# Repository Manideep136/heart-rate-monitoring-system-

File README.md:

# heart-rate-monitoring-system

## 📌 Project Overview

The **Heart Rate Monitoring System** is an electronics project designed to measure a person's heart rate in beats per minute (BPM) using a heart rate sensor. The system processes the sensor signal and displays the measured heart rate for easy monitoring.

This project focuses on sensor interfacing, signal processing, microcontroller-based measurement, and electronic circuit design.

## 🎯 Project Objectives

- Measure heart rate in beats per minute (BPM).
- Interface a heart rate sensor with a microcontroller.
- Process sensor signals to estimate heart rate.
- Display the measured heart rate on a suitable output device.
- Design a compact and organized electronic circuit or PCB.
- Develop practical skills in embedded systems and electronics.

## ⚙️ Working Principle

1. **Signal Detection:** The heart rate sensor detects changes associated with blood flow, typically using optical sensing.
2. **Signal Processing:** The sensor signal is processed to identify pulse events.
3. **Heart Rate Calculation:** The system estimates the heart rate in BPM based on the detected pulse intervals.
4. **Output Display:** The calculated heart rate is displayed on an LCD, OLED, serial monitor, or other supported output.
5. **Continuous Monitoring:** The system can repeatedly update the reading while the sensor detects a reliable signal.

### Block Diagram

```text
     Human Finger
          │
          ▼
   Heart Rate Sensor
          │
          ▼
    Microcontroller
          │
          ▼
   Signal Processing
          │
          ▼
   BPM Calculation
          │
          ▼
    Display / Output
```

## 🔧 Main Components

| Component | Function |
|---|---|
| Heart rate sensor | Detects pulse-related signals |
| Microcontroller | Processes sensor data and calculates BPM |
| Display module | Displays the measured heart rate, if used |
| Resistors and capacitors | Support signal conditioning and circuit operation, where required |
| Power supply | Provides the required operating voltage |
| PCB | Provides component mounting and electrical connections |

*The exact components depend on the hardware used in the final design.*

## 🖥️ Software and Tools

- KiCad – Schematic and PCB design, if applicable
- Arduino IDE or PlatformIO – Microcontroller programming, if applicable
- Microcontroller development environment
- Sensor libraries and documentation
- Serial Monitor for debugging and observing readings

## 🧩 Design Workflow

### 1. Circuit Design
Create the circuit schematic with the heart rate sensor, microcontroller, power supply, and output interface.

### 2. Component Selection
Select components based on operating voltage, communication interface, package type, and datasheet specifications.

### 3. Footprint Assignment
Assign appropriate footprints to the components and verify their dimensions and pin numbering.

### 4. PCB Layout
Arrange the components and route the required power and signal connections. Keep sensor signal paths away from noisy switching or power circuits where practical.

### 5. Programming and Interfacing
Develop the firmware to read the sensor data, identify pulse events, and calculate BPM.

### 6. Design Verification
Check the schematic and PCB for connection errors, clearances, footprint mismatches, and other design issues.

### 7. Testing
Compare readings with a suitable reference device under consistent conditions. Record the observed results before claiming accuracy or successful validation.

## 📐 Important Design Considerations

- Verify the sensor's supply voltage and logic-level requirements.
- Ensure correct sensor pin connections.
- Use appropriate filtering or signal-processing techniques.
- Avoid loose sensor contact and excessive movement during measurements.
- Provide stable power to the sensor and microcontroller.
- Verify the PCB footprints against component datasheets.
- Include test points where useful for debugging.
- Handle invalid or unreliable sensor readings appropriately.

```

*Include only the files that are part of your actual project.*

## 🚀 Future Improvements

- Add an OLED display for real-time BPM readings.
- Add Bluetooth or Wi-Fi connectivity for data transmission.
- Store readings for later analysis.
- Add low-signal and sensor-disconnection indicators.
- Develop a mobile dashboard for viewing measurements.
- Optimize PCB size and power consumption.

## 📚 Learning Outcomes

This project helps develop skills in:

- Sensor interfacing
- Embedded C/C++ programming
- Microcontroller-based data acquisition
- Basic signal processing
- Heart rate calculation
- Electronic schematic and PCB design
- Component selection and footprint verification
- Circuit debugging and testing

## ⚠️ Disclaimer

This project is intended for educational and experimental purposes. It is not a medical device and must not be used to diagnose, monitor, or treat medical conditions. Readings may be affected by movement, sensor placement, ambient light, and other factors.

## 🛠️ Project Information

- **Project Name:** Heart Rate Monitoring System
- **Domain:** Embedded Systems / Biomedical Electronics
- **Project Type:** Electronics and Sensor-Based Monitoring
- **Design Tool:** KiCad, if used for PCB design
- **Controller and Sensor:** Specify the actual components used

---

*This repository documents the design and implementation of a heart rate monitoring system. Update the project details, images, and testing status to match your completed work.*

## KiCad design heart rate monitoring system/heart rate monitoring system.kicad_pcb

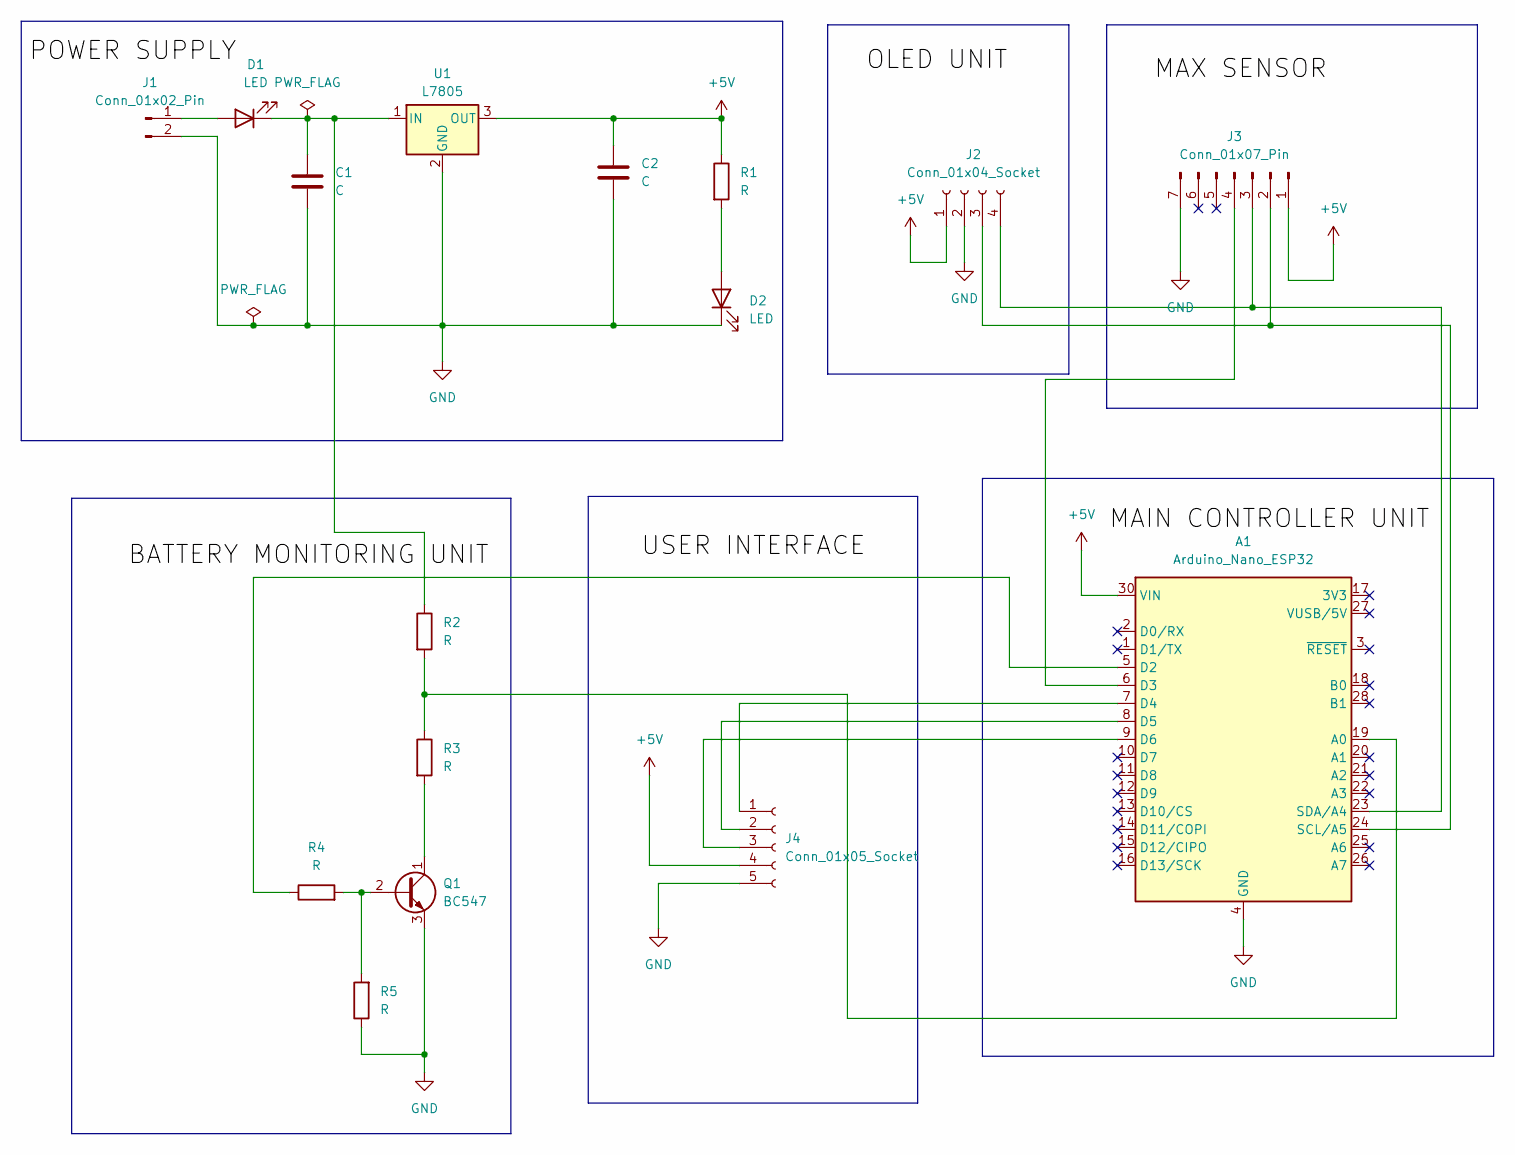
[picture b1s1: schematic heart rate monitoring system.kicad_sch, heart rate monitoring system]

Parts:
A1: Arduino_Nano_ESP32; Arduino_Nano
C1, C2: C; CP_Radial_D8.0mm_P2.50mm
D1, D2: LED; LED_D5.0mm
J1: Conn_01x02_Pin; PinHeader_1x02_P2.54mm_Vertical
J2: Conn_01x04_Socket; Stocko_MKS_1654-6-0-404_1x4_P2.50mm_Vertical
J3: Conn_01x07_Pin; Stocko_MKS_1657-6-0-707_1x7_P2.50mm_Vertical
J4: Conn_01x05_Socket; Stocko_MKS_1655-6-0-505_1x5_P2.50mm_Vertical
Q1: BC547; TO-92_Inline
R1, R2, R3, R4, R5: R; R_Axial_DIN0309_L9.0mm_D3.2mm_P15.24mm_Horizontal
U1: L7805; TO-220-3_Vertical

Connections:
+5V: A1.30 (VIN), C2.1, J2.1, J3.1, J4.4, R1.1, U1.3 (OUT)
GND: A1.4 (GND), A1.29 (GND), C1.2, C2.2, D2.1 (K), J1.2, J2.2, J3.7, J4.5, Q1.3 (E), R5.1, U1.2 (GND)
unnamed: A1.19 (A0), R2.2, R3.1
unnamed: A1.5 (D2), R4.1
unnamed: A1.6 (D3), J3.4
unnamed: A1.7 (D4), J4.1
unnamed: A1.8 (D5), J4.2
unnamed: A1.9 (D6), J4.3
unnamed: A1.24 (SCL/A5), J2.3, J3.2
unnamed: A1.23 (SDA/A4), J2.4, J3.3
unnamed: D1.2 (A), J1.1
unnamed: C1.1, D1.1 (K), R2.1, U1.1 (IN)
unnamed: D2.2 (A), R1.2
unnamed: Q1.2 (B), R4.2, R5.2
unnamed: Q1.1 (C), R3.2

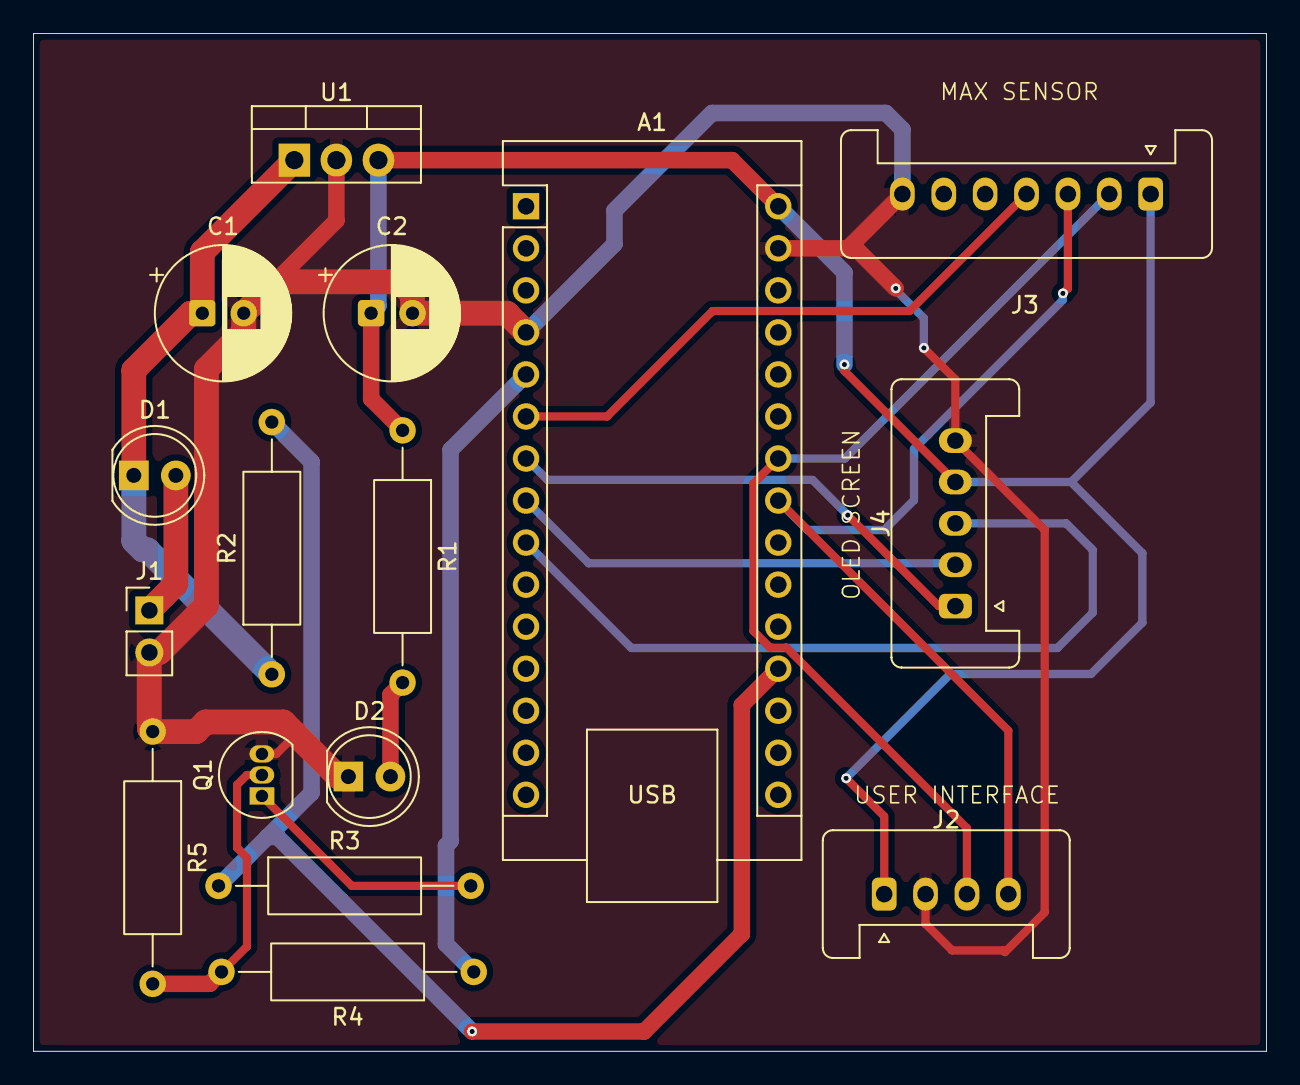
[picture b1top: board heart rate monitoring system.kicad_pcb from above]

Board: 2 copper layers, 74.5 x 61.5 mm, 16 parts (0 on the bottom side), 15 nets.
